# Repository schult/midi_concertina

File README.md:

# MIDI Anglo Concertina

This is a 30-button Anglo Concertina MIDI controller. Click the image below to
watch a short demo:

[Build Instructions](mechanical/README.md)

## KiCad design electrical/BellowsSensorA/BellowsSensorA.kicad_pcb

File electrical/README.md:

# MIDI Concertina - Electrical

These boards are designed to be produced using [JLCPCB](jlcpcb.com)'s Economic
PCBA service. I recommend exporting them with
[Fabrication Toolkit](https://github.com/bennymeg/Fabrication-Toolkit).

## License

[CERN Open Hardware Licence Version 2 - Strongly Reciprocal](LICENSE.txt)

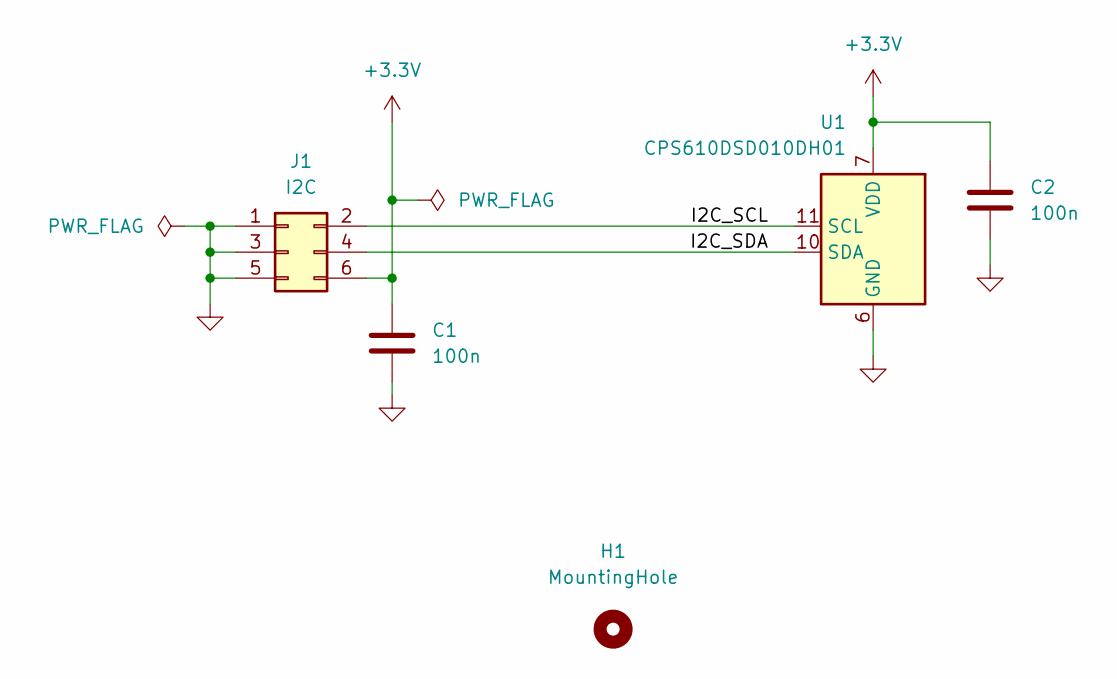
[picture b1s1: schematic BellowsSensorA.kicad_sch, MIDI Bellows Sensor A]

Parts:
C1, C2: 100n; C_0402_1005Metric; Part Samsung CL05B104KO5NNNC; LCSC C1525
H1: MountingHole; MountingHole_3.2mm_M3
J1: I2C; Wuerth_WR-WST_490107670612_2x03_P2.54mm_SKEDD
U1: CPS610DSD010DH01; SOIC-16W_7.5x10.3mm_P1.27mm; Part Consensic CPS610DSD010DH01; LCSC C28646450

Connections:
+3.3V: C1.1, C2.1, J1.6, U1.7 (VDD)
/I2C_SCL: J1.2, U1.11 (SCL)
/I2C_SDA: J1.4, U1.10 (SDA)
GND: C1.2, C2.2, J1.1, J1.3, J1.5, U1.6 (GND)

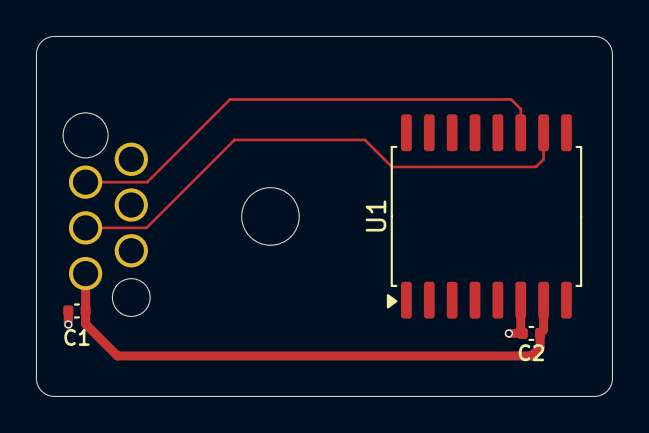
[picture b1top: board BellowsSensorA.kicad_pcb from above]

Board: 2 copper layers, 32.0 x 20.0 mm, 5 parts (1 on the bottom side), 4 nets.

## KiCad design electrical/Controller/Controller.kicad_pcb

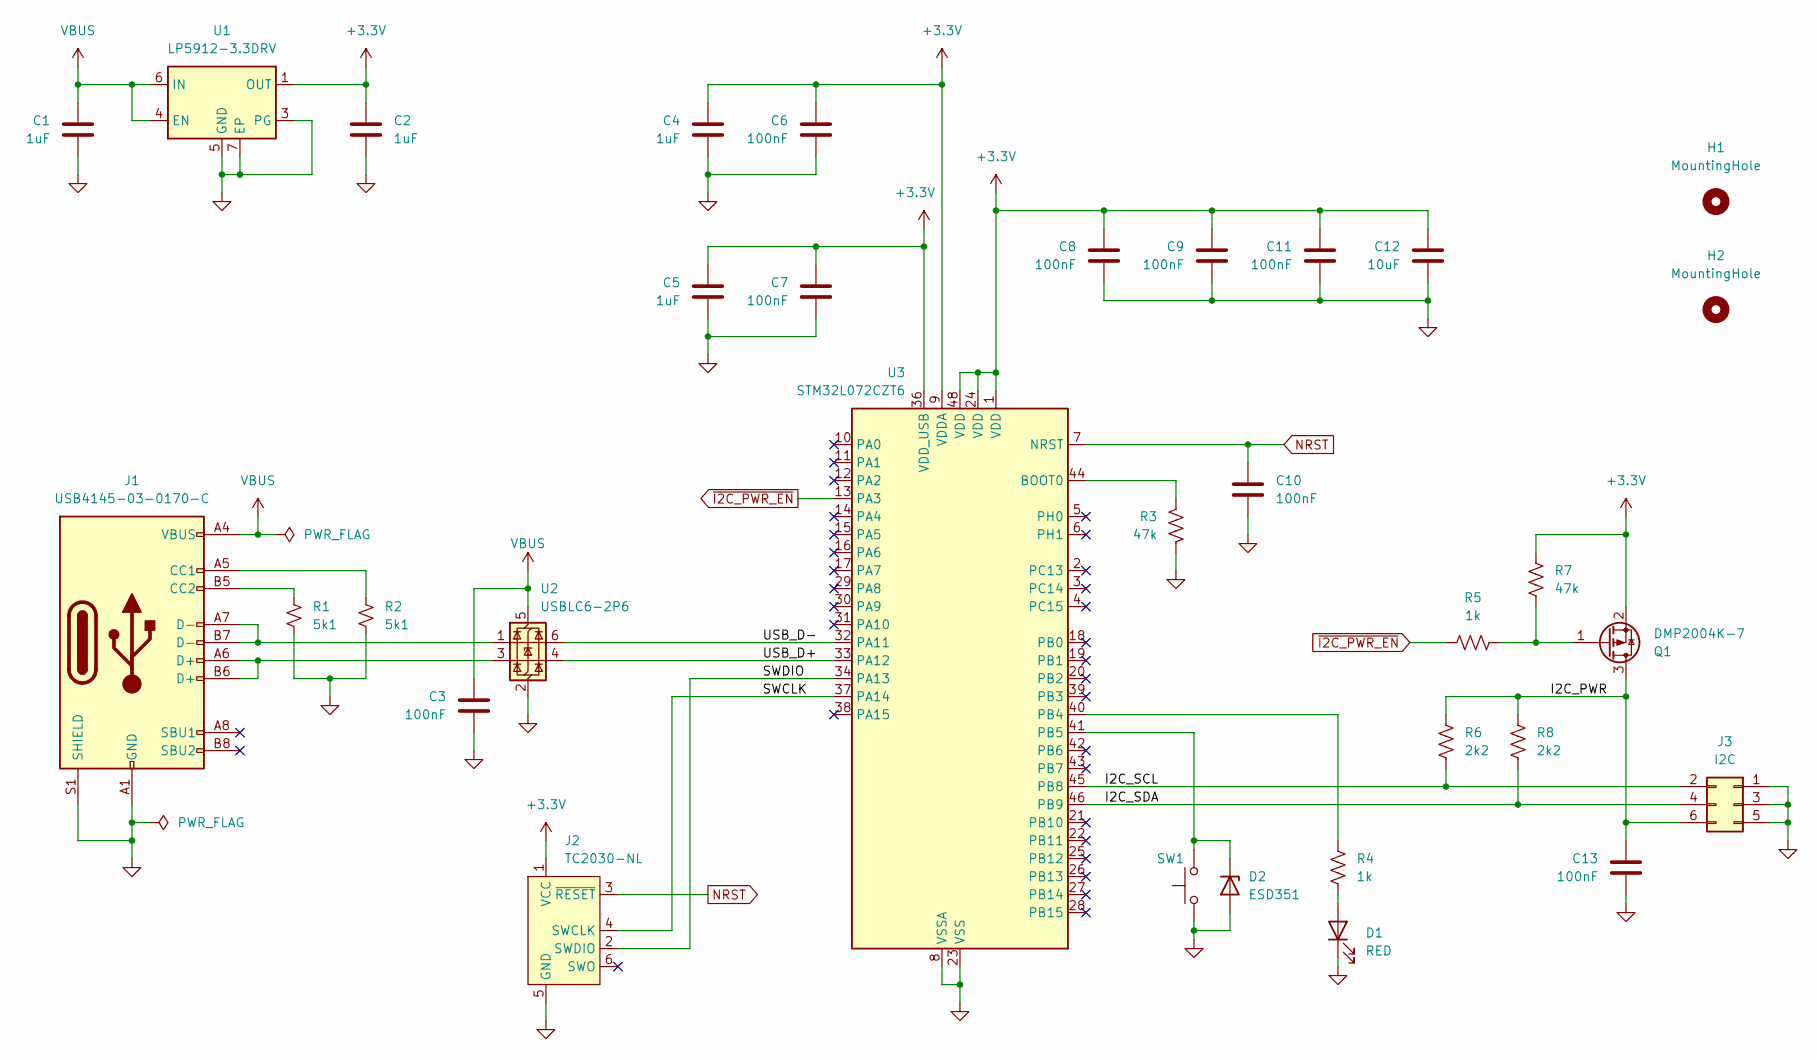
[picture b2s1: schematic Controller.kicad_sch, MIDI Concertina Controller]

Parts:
C1, C2, C4, C5: 1uF; C_0402_1005Metric; Part Samsung CL05A105KA5NQNC; LCSC C52923
C3, C6, C7, C8, C9, C10, C11, C13: 100nF; C_0402_1005Metric; Part Samsung CL05B104KO5NNNC; LCSC C1525
C12: 10uF; C_0603_1608Metric; Part Samsung CL10A106MA8NRNC; LCSC C96446
D1: RED; LED_0603_1608Metric; Part KENTO KT-0603R; LCSC C2286
D2: ESD351; Texas_DPY0002A_0.6x1mm_P0.65mm; Part TI ESD351DPYR; LCSC C1974929
H1, H2: MountingHole; MountingHole_3.2mm_M3
J1: USB4145-03-0170-C; USB_C_Receptacle_GCT-USB4145; Part GCT USB4145-03-0170-C; LCSC C5181332
J2: TC2030-NL; Tag-Connect_TC2030-IDC-NL_2x03_P1.27mm_Vertical
J3: I2C; Wuerth_WR-WST_490107670612_2x03_P2.54mm_SKEDD
Q1: DMP2004K-7; SOT-23; Part Diodes Incorporated DMP2004K-7; LCSC C332297
R1, R2: 5k1; R_0603_1608Metric; Part UNI-ROYAL 0603WAF5101T5E; LCSC C23186
R3, R7: 47k; R_0402_1005Metric; Part UNI-ROYAL 0402WGF4702TCE; LCSC C25792
R4, R5: 1k; R_0402_1005Metric; Part UNI-ROYAL 0402WGF1001TCE; LCSC C11702
R6, R8: 2k2; R_0603_1608Metric; Part UNI-ROYAL 0603WAF2201T5E; LCSC C4190
SW1: SW_Push_1P1T_NO_E-Switch_TL3301NxxxxxG; Part E-Switch TL3301AF160QG; LCSC C273519
U1: LP5912-3.3DRV; WSON-6-1EP_2x2mm_P0.65mm_EP1x1.6mm_ThermalVias; Part TI LP5912-3.3DRVR; LCSC C524780
U2: USBLC6-2P6; SOT-666; Part ST USBLC6-2P6; LCSC C15999
U3: STM32L072CZT6; LQFP-48_7x7mm_P0.5mm; Part STM32L072CZT6; LCSC C1337587

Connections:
+3.3V: C2.1, C4.1, C5.1, C6.1, C7.1, C8.1, C9.1, C11.1, C12.1, J2.1 (VCC), Q1.2 (S), R7.1, U1.1 (OUT), U3.1 (VDD), U3.9 (VDDA), U3.24 (VDD), U3.36 (VDD_USB), U3.48 (VDD)
/I2C_PWR: C13.1, J3.6, Q1.3 (D), R6.1, R8.1
/I2C_SCL: J3.2, R6.2, U3.45 (PB8)
/I2C_SDA: J3.4, R8.2, U3.46 (PB9)
/SWCLK: J2.4 (SWCLK), U3.37 (PA14)
/SWDIO: J2.2 (SWDIO), U3.34 (PA13)
/USB_D+: U2.4 (I/O2), U3.33 (PA12)
/USB_D-: U2.6 (I/O1), U3.32 (PA11)
GND: C1.2, C2.2, C3.2, C4.2, C5.2, C6.2, C7.2, C8.2, C9.2, C10.2, C11.2, C12.2, C13.2, D1.1 (K), D2.2 (A), J1.A1 (GND), J1.A12 (GND), J1.B1 (GND), J1.B12 (GND), J1.S1 (SHIELD), J2.5 (GND), J3.1, J3.3, J3.5, R1.2, R2.2, R3.2, SW1.2, U1.3 (PG), U1.5 (GND), U1.7 (EP), U2.2 (GND), U3.8 (VSSA), U3.23 (VSS), U3.35 (VSS), U3.47 (VSS)
NRST: C10.1, J2.3 (~RESET), U3.7 (NRST)
unnamed: D1.2 (A), R4.2
unnamed: D2.1 (K), SW1.1, U3.41 (PB5)
unnamed: J1.A5 (CC1), R2.1
unnamed: J1.B5 (CC2), R1.1
unnamed: J1.A6 (D+), J1.B6 (D+), U2.3 (I/O2)
unnamed: J1.A7 (D-), J1.B7 (D-), U2.1 (I/O1)
unnamed: Q1.1 (G), R5.2, R7.2
unnamed: R3.1, U3.44 (BOOT0)
unnamed: R4.1, U3.40 (PB4)
VBUS: C1.1, C3.1, J1.A4 (VBUS), J1.A9 (VBUS), J1.B4 (VBUS), J1.B9 (VBUS), U1.4 (EN), U1.6 (IN), U2.5 (VBUS)
~I2C_PWR_EN: R5.1, U3.13 (PA3)

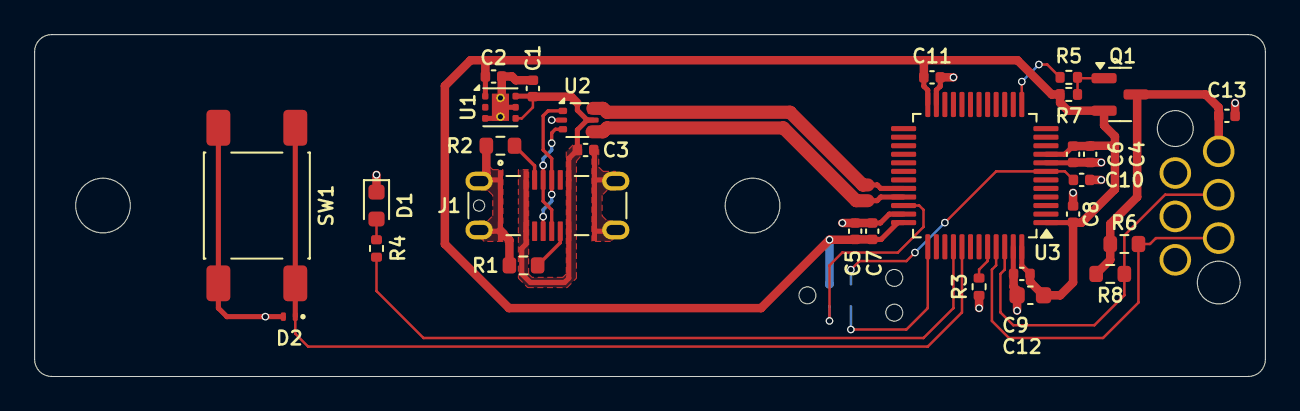
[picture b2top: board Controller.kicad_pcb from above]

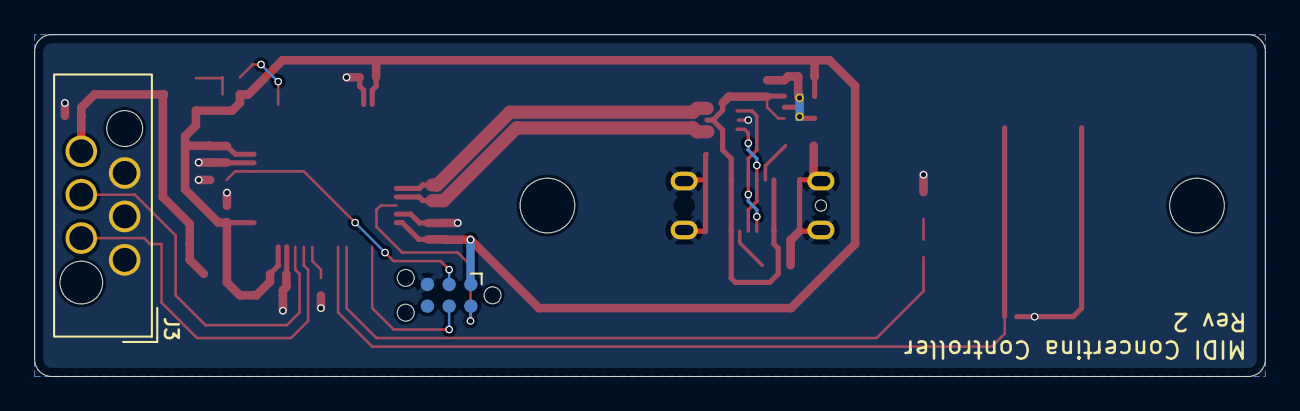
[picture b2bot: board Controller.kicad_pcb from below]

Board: 2 copper layers, 72.0 x 20.0 mm, 33 parts (2 on the bottom side), 21 nets.

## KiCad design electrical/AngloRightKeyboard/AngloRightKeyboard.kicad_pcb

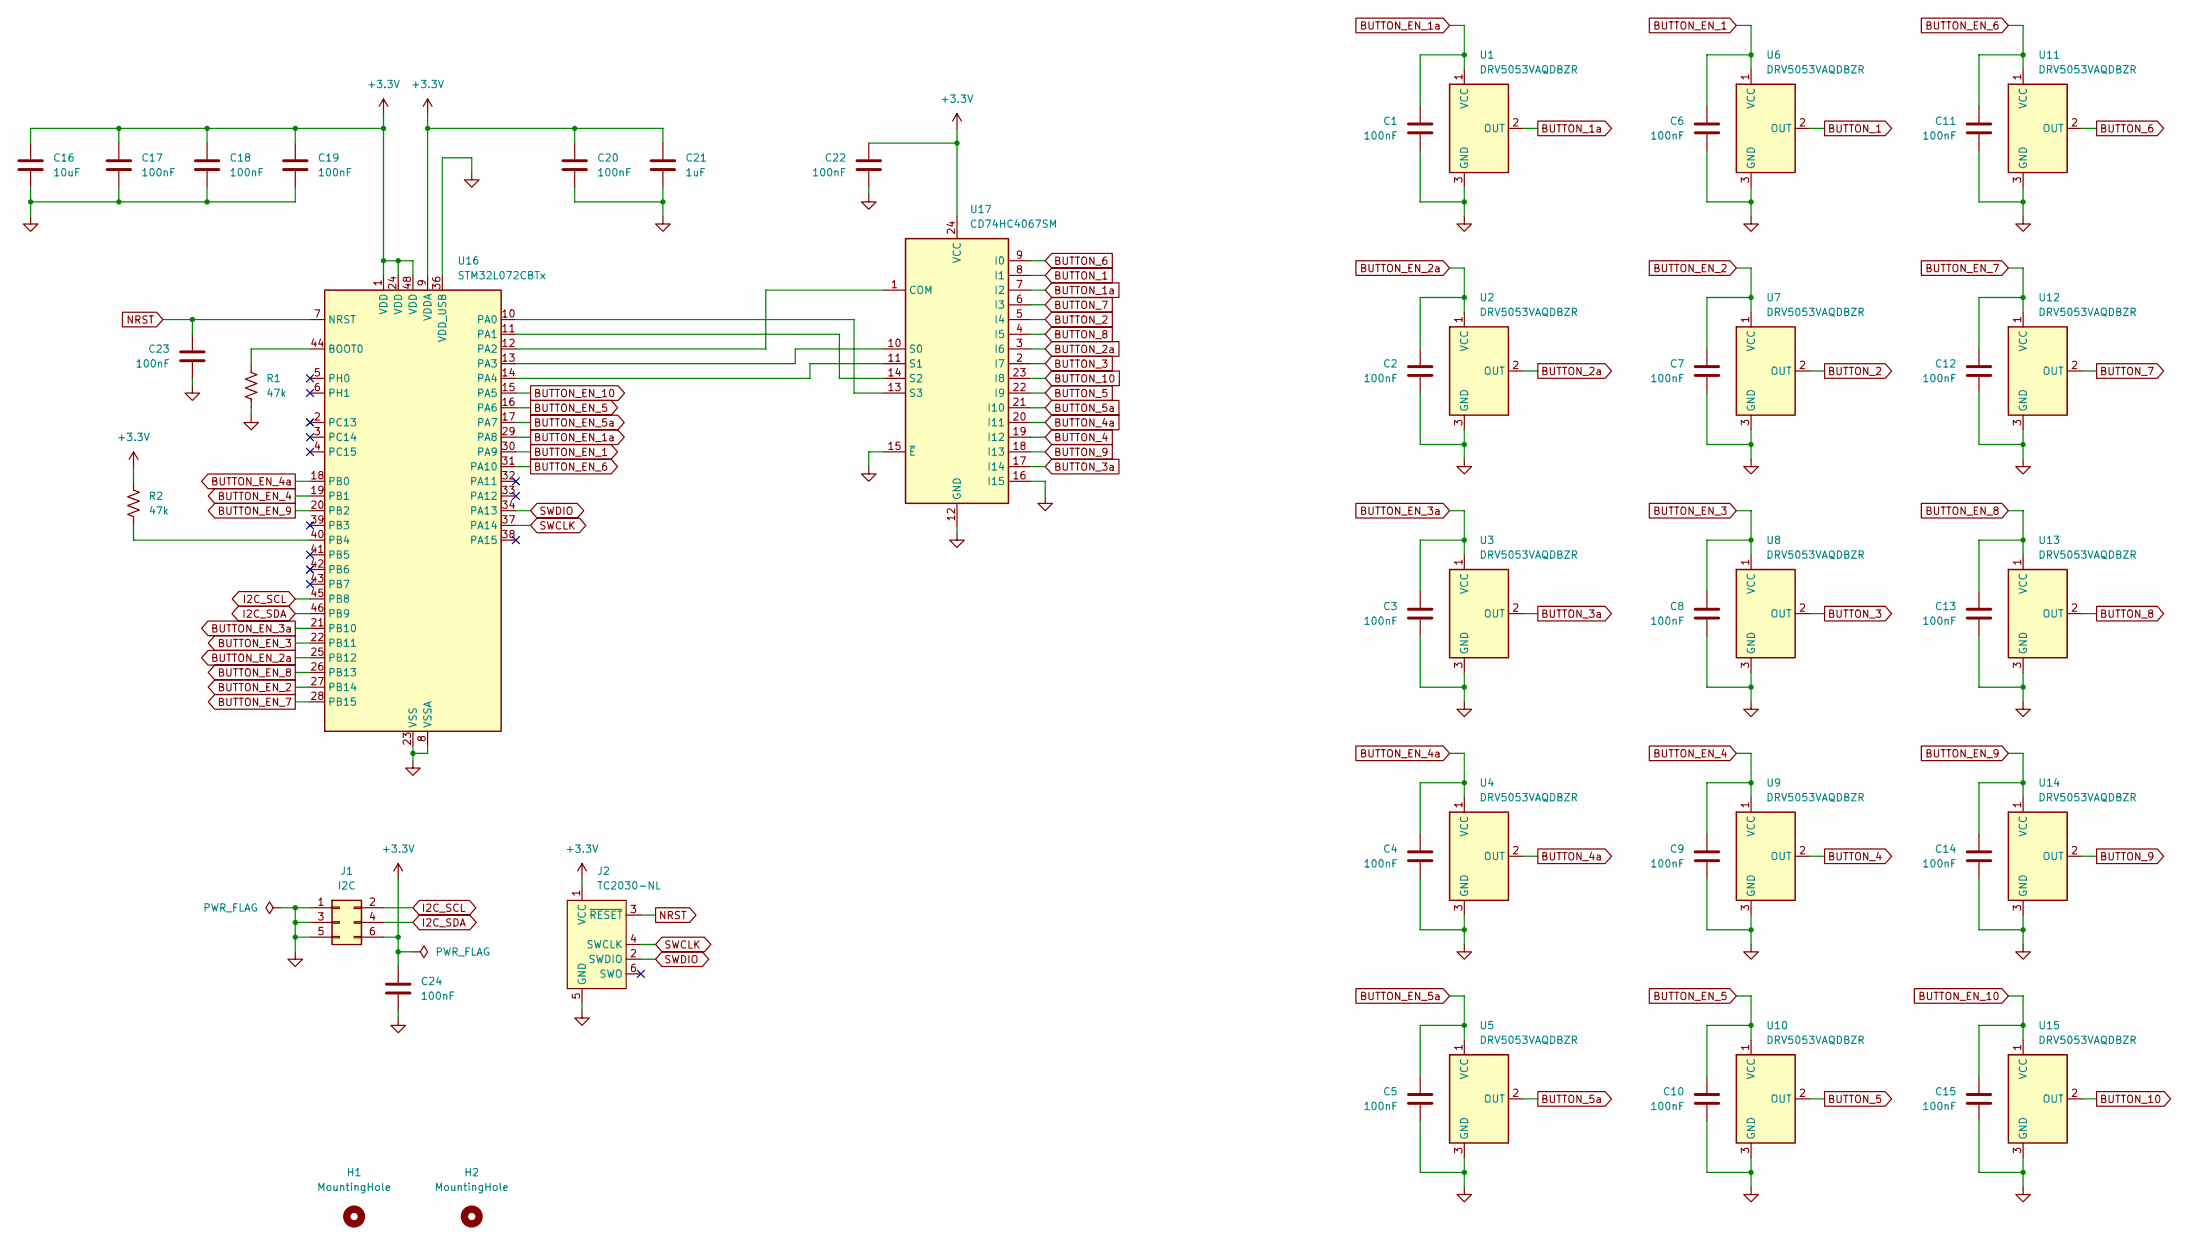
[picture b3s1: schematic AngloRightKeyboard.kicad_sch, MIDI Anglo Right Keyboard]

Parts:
C1, C2, C3, C4, C5, C6, C7, C8, C9, C10, C11, C12, C13, C14, C15, C17, C18, C19, C20, C22, C23, C24: 100nF; C_0402_1005Metric; Part Samsung CL05B104KO5NNNC; LCSC C1525
C16: 10uF; C_0603_1608Metric; Part Samsung CL10A106MA8NRNC; LCSC C96446
C21: 1uF; C_0402_1005Metric; Part Samsung CL05A105KA5NQNC; LCSC C52923
H1, H2: MountingHole; MountingHole_3.2mm_M3
J1: I2C; Wuerth_WR-WST_490107670612_2x03_P2.54mm_SKEDD
J2: TC2030-NL; Tag-Connect_TC2030-IDC-NL_2x03_P1.27mm_Vertical
R1, R2: 47k; R_0402_1005Metric; Part UNI-ROYAL 0402WGF4702TCE; LCSC C25792
U1, U2, U3, U4, U5, U6, U7, U8, U9, U10, U11, U12, U13, U14, U15: DRV5053VAQDBZR; SOT-23; Part TI DRV5053VAQDBZR; LCSC C962159
U16: STM32L072CBTx; LQFP-48_7x7mm_P0.5mm; Part STM32L072CBT6; LCSC C465977
U17: CD74HC4067SM; SSOP-24_5.3x8.2mm_P0.65mm; Part TI CD74HC4067SM96; LCSC C98457

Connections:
+3.3V: C16.1, C17.1, C18.1, C19.1, C20.1, C21.1, C22.1, C24.1, J1.6, J2.1 (VCC), R2.1, U16.1 (VDD), U16.9 (VDDA), U16.24 (VDD), U16.48 (VDD), U17.24 (VCC)
BUTTON_1: U6.2 (OUT), U17.8 (I1)
BUTTON_1a: U1.2 (OUT), U17.7 (I2)
BUTTON_2: U7.2 (OUT), U17.5 (I4)
BUTTON_2a: U2.2 (OUT), U17.3 (I6)
BUTTON_3: U8.2 (OUT), U17.2 (I7)
BUTTON_3a: U3.2 (OUT), U17.17 (I14)
BUTTON_4: U9.2 (OUT), U17.19 (I12)
BUTTON_4a: U4.2 (OUT), U17.20 (I11)
BUTTON_5: U10.2 (OUT), U17.22 (I9)
BUTTON_5a: U5.2 (OUT), U17.21 (I10)
BUTTON_6: U11.2 (OUT), U17.9 (I0)
BUTTON_7: U12.2 (OUT), U17.6 (I3)
BUTTON_8: U13.2 (OUT), U17.4 (I5)
BUTTON_9: U14.2 (OUT), U17.18 (I13)
BUTTON_10: U15.2 (OUT), U17.23 (I8)
BUTTON_EN_1: C6.1, U6.1 (VCC), U16.30 (PA9)
BUTTON_EN_1a: C1.1, U1.1 (VCC), U16.29 (PA8)
BUTTON_EN_2: C7.1, U7.1 (VCC), U16.27 (PB14)
BUTTON_EN_2a: C2.1, U2.1 (VCC), U16.25 (PB12)
BUTTON_EN_3: C8.1, U8.1 (VCC), U16.22 (PB11)
BUTTON_EN_3a: C3.1, U3.1 (VCC), U16.21 (PB10)
BUTTON_EN_4: C9.1, U9.1 (VCC), U16.19 (PB1)
BUTTON_EN_4a: C4.1, U4.1 (VCC), U16.18 (PB0)
BUTTON_EN_5: C10.1, U10.1 (VCC), U16.16 (PA6)
BUTTON_EN_5a: C5.1, U5.1 (VCC), U16.17 (PA7)
BUTTON_EN_6: C11.1, U11.1 (VCC), U16.31 (PA10)
BUTTON_EN_7: C12.1, U12.1 (VCC), U16.28 (PB15)
BUTTON_EN_8: C13.1, U13.1 (VCC), U16.26 (PB13)
BUTTON_EN_9: C14.1, U14.1 (VCC), U16.20 (PB2)
BUTTON_EN_10: C15.1, U15.1 (VCC), U16.15 (PA5)
GND: C1.2, C2.2, C3.2, C4.2, C5.2, C6.2, C7.2, C8.2, C9.2, C10.2, C11.2, C12.2, C13.2, C14.2, C15.2, C16.2, C17.2, C18.2, C19.2, C20.2, C21.2, C22.2, C23.2, C24.2, J1.1, J1.3, J1.5, J2.5 (GND), R1.2, U1.3 (GND), U2.3 (GND), U3.3 (GND), U4.3 (GND), U5.3 (GND), U6.3 (GND), U7.3 (GND), U8.3 (GND), U9.3 (GND), U10.3 (GND), U11.3 (GND), U12.3 (GND), U13.3 (GND), U14.3 (GND), U15.3 (GND), U16.8 (VSSA), U16.23 (VSS), U16.35 (VSS), U16.36 (VDD_USB), U16.47 (VSS), U17.12 (GND), U17.15 (~E), U17.16 (I15)
I2C_SCL: J1.2, U16.45 (PB8)
I2C_SDA: J1.4, U16.46 (PB9)
NRST: C23.1, J2.3 (~RESET), U16.7 (NRST)
unnamed: R1.1, U16.44 (BOOT0)
unnamed: U16.10 (PA0), U17.13 (S3)
unnamed: U16.11 (PA1), U17.14 (S2)
unnamed: U16.12 (PA2), U17.1 (COM)
unnamed: U16.13 (PA3), U17.10 (S0)
unnamed: U16.14 (PA4), U17.11 (S1)
unnamed: R2.2, U16.40 (PB4)
SWCLK: J2.4 (SWCLK), U16.37 (PA14)
SWDIO: J2.2 (SWDIO), U16.34 (PA13)

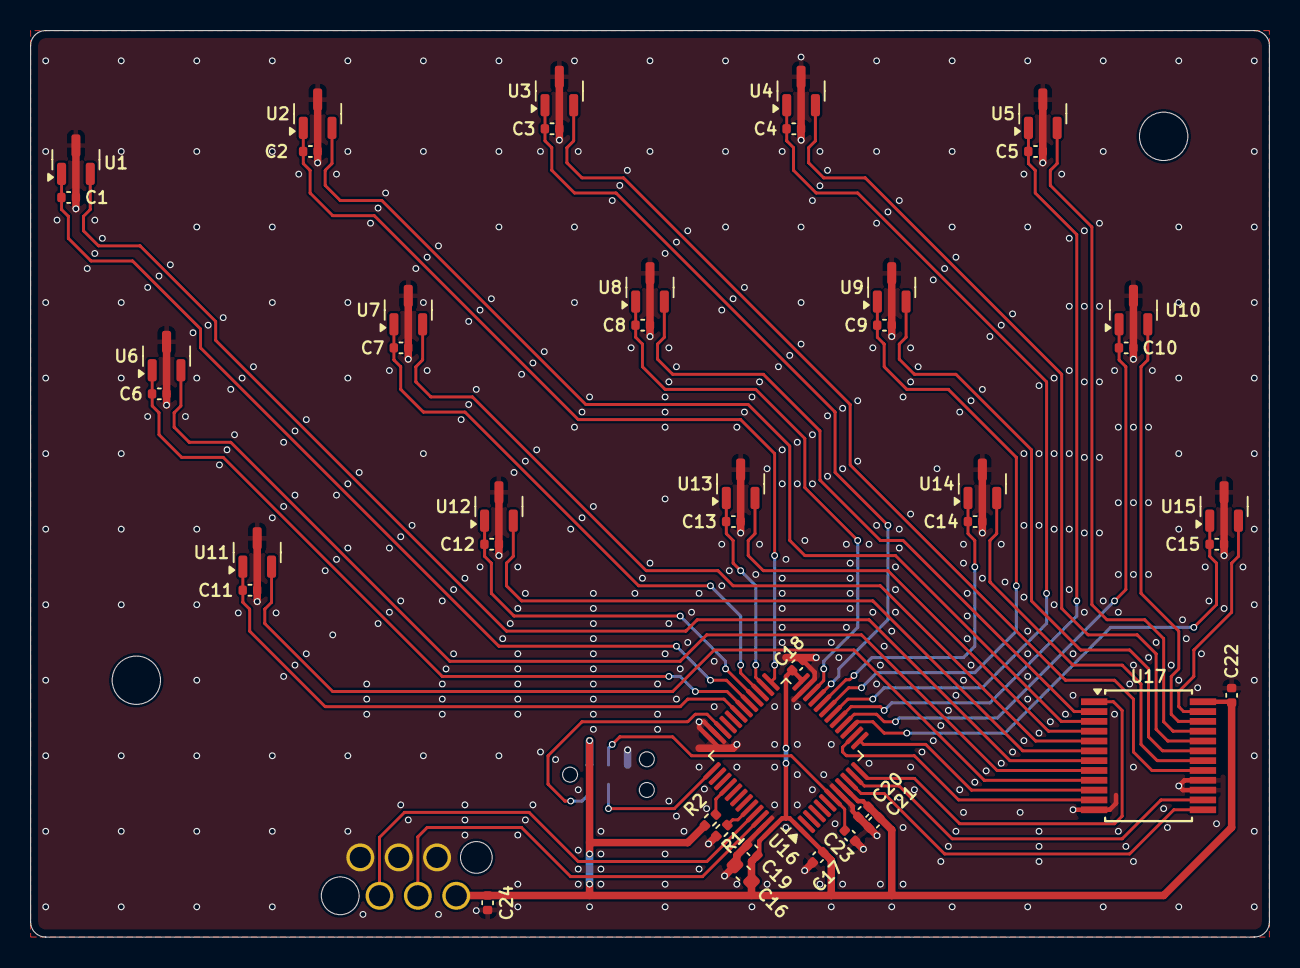
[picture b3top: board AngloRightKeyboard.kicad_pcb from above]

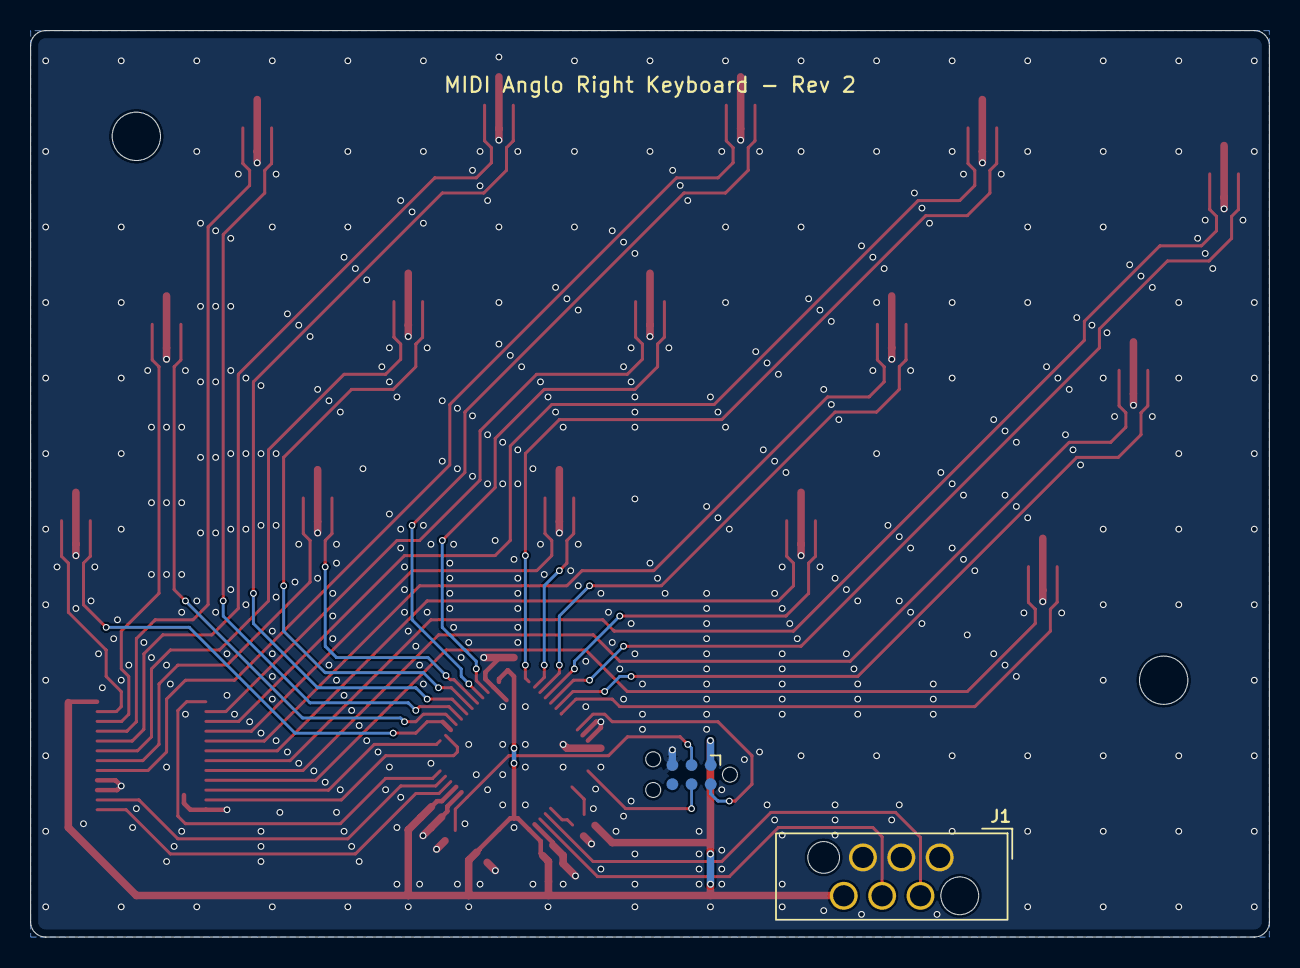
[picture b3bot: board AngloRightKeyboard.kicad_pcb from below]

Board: 2 copper layers, 82.0 x 60.0 mm, 47 parts (2 on the bottom side), 44 nets.

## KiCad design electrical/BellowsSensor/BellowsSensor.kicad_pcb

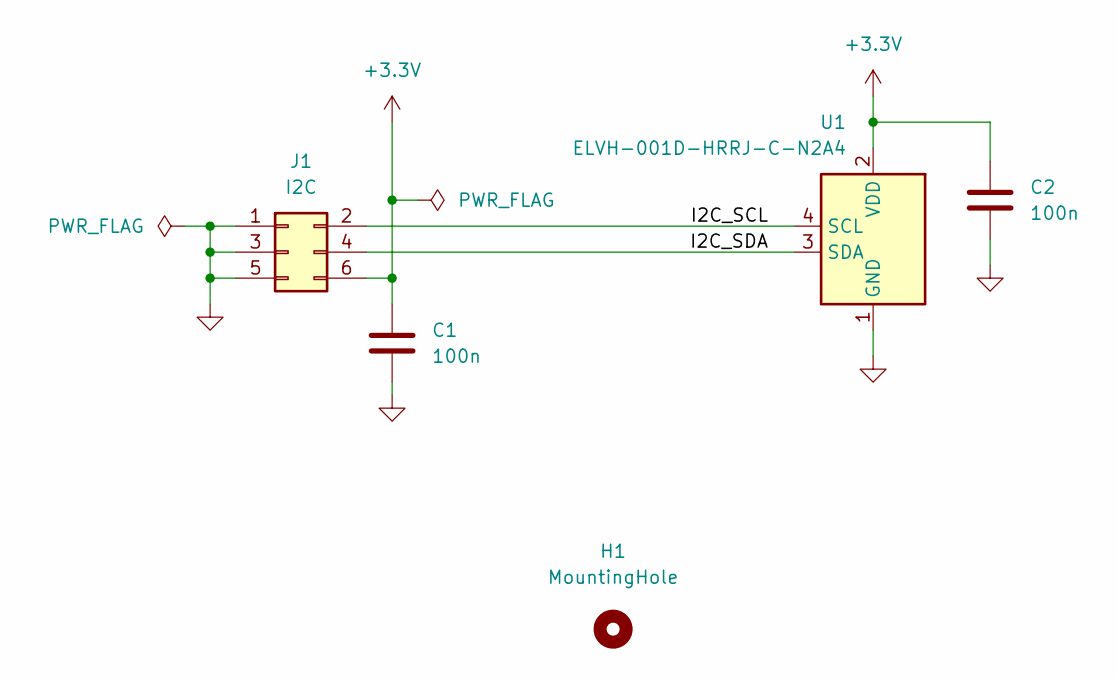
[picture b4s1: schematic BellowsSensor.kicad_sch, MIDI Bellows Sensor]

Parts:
C1, C2: 100n; C_0402_1005Metric; Part Samsung CL05B104KO5NNNC; LCSC C1525
H1: MountingHole; MountingHole_3.2mm_M3
J1: I2C; Wuerth_WR-WST_490107670612_2x03_P2.54mm_SKEDD
U1: ELVH-001D-HRRJ-C-N2A4; Amphenol_ELVH-x-xJ-x-x; Part Amphenol ELVH-001D-HRRJ-C-N2A4; LCSC C3241336

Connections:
+3.3V: C1.1, C2.1, J1.6, U1.2 (VDD)
/I2C_SCL: J1.2, U1.4 (SCL)
/I2C_SDA: J1.4, U1.3 (SDA)
GND: C1.2, C2.2, J1.1, J1.3, J1.5, U1.1 (GND)

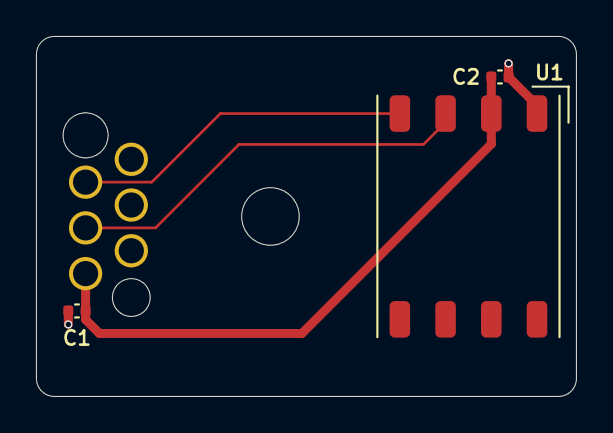
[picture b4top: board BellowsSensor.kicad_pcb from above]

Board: 2 copper layers, 30.0 x 20.0 mm, 5 parts (1 on the bottom side), 4 nets.

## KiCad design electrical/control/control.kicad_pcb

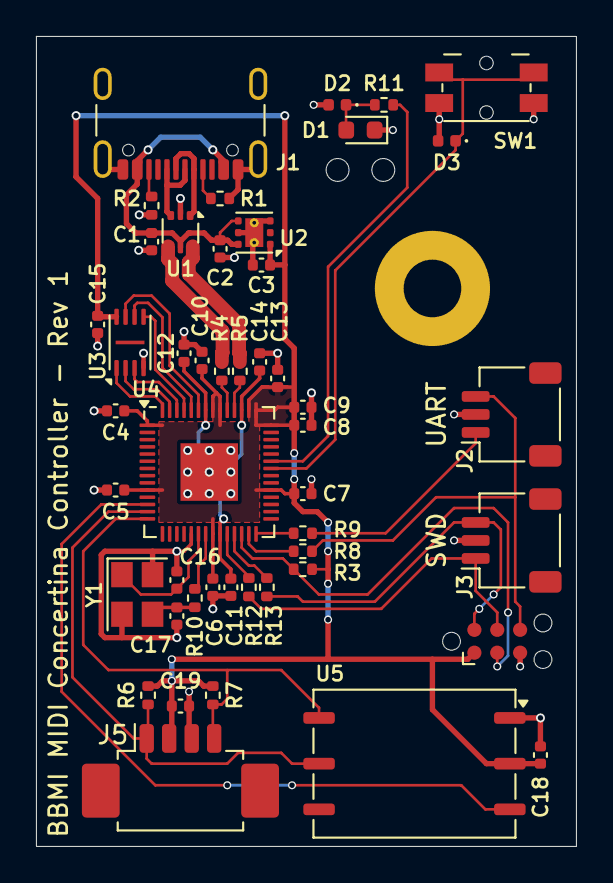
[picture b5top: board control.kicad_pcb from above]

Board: 2 copper layers, 30.0 x 45.0 mm, 49 parts (0 on the bottom side), 36 nets.

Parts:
C1, C4, C5, C6, C7, C8, C9, C10, C11, C12, C15, C18, C19: 100n; C_0402_1005Metric
C2, C3, C13, C14: 1uF; C_0402_1005Metric
C16, C17: 15p; C_0402_1005Metric
D1: RED; LED_0603_1608Metric
D2, D3: ESD351; D_0402_1005Metric
H1: MountingHole; MountingHole_3.2mm_M3_Pad
H2: SLP-150-150-F; SLP3-150-150-F
J1: USB4105-GF-A; USB_C_Receptacle_GCT_USB4105-xx-A_16P_TopMnt_Horizontal
J2: UART; JST_SH_SM03B-SRSS-TB_1x03-1MP_P1.00mm_Horizontal
J3: SWD; JST_SH_SM03B-SRSS-TB_1x03-1MP_P1.00mm_Horizontal
J4: TC2030-NL; Tag-Connect_TC2030-IDC-NL_2x03_P1.27mm_Vertical
J5: I2C; Molex_PicoBlade_53261-0471_1x04-1MP_P1.25mm_Horizontal
R1, R2: 5k1; R_0402_1005Metric
R3, R10, R11: 1k; R_0402_1005Metric
R4, R5: 27R; R_0402_1005Metric
R6, R7: 2k2; R_0402_1005Metric
R8, R9, R12, R13: 100R; R_0402_1005Metric
SW1: SYS; Panasonic_EVQPUL_EVQPUC
U1: USBLC6-2P6; SOT-666
U2: LP5912-3.3DRV; WSON-6-1EP_2x2mm_P0.65mm_EP1x1.6mm_ThermalVias
U3: W25Q16JVUXIQ; Winbond_USON-8-1EP_3x2mm_P0.5mm_EP0.2x1.6mm
U4: RP2040; QFN-56-1EP_7x7mm_P0.4mm_EP3.2x3.2mm
U5: ABPMRRV060MG2A3; Honeywell_ABPMRRx
Y1: ABM8-272-T3; Crystal_SMD_3225-4Pin_3.2x2.5mm

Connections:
+1V1: C11.1, C12.1, C14.1, U4.23 (DVDD), U4.45 (VREG_VOUT), U4.50 (DVDD)
+3.3V: C3.1, C4.1, C5.1, C6.1, C7.1, C8.1, C9.1, C10.1, C13.1, C15.1, C18.1, C19.1, J4.1 (VCC), J5.2, R3.1, R6.1, R7.1, U2.1 (OUT), U3.8 (VCC), U4.1 (IOVDD), U4.10 (IOVDD), U4.22 (IOVDD), U4.33 (IOVDD), U4.42 (IOVDD), U4.43 (ADC_AVDD), U4.44 (VREG_IN), U4.48 (USB_VDD), U4.49 (IOVDD), U5.2 (VDD)
/QSPI_SCLK: U3.6 (CLK), U4.52 (QSPI_SCLK)
/QSPI_SD0: U3.5 (DI/IO_{0}), U4.53 (QSPI_SD0)
/QSPI_SD1: U3.2 (DO/IO_{1}), U4.55 (QSPI_SD1)
/QSPI_SD2: U3.3 (~WP/IO_{2}), U4.54 (QSPI_SD2)
/QSPI_SD3: U3.7 (~HOLD/~RESET/IO_{3}), U4.51 (QSPI_SD3)
/QSPI_SS: U3.1 (~CS), U4.56 (QSPI_SS)
GND: C1.2, C2.2, C3.2, C4.2, C5.2, C6.2, C7.2, C8.2, C9.2, C10.2, C11.2, C12.2, C13.2, C14.2, C15.2, C16.2, C17.2, C18.2, C19.2, D1.1 (K), D2.2 (A), D3.2 (A), H1.1, J1.A1 (GND), J1.A12 (GND), J1.B1 (GND), J1.B12 (GND), J1.S1 (SHIELD), J2.2, J3.2, J4.5 (GND), J5.3, R1.2, R2.2, SW1.2, U1.2 (GND), U2.3 (PG), U2.5 (GND), U2.7 (EP), U3.4 (GND), U4.19 (TESTEN), U4.57 (GND), U5.1 (GND), Y1.2, Y1.4
I2C_SCL: J5.4, R7.2, U4.14 (GPIO11), U5.6 (SCL)
I2C_SDA: J5.1, R6.2, U4.13 (GPIO10), U5.5 (SDA)
unnamed: C17.1, R10.1, Y1.3
unnamed: D1.2 (A), D2.1 (K), R11.2
unnamed: D3.1 (K), SW1.1, U4.36 (GPIO24)
unnamed: J1.A5 (CC1), R1.1
unnamed: J1.B5 (CC2), R2.1
unnamed: J1.A6 (D+), J1.B6 (D+), U1.3 (I/O2)
unnamed: J1.A7 (D-), J1.B7 (D-), U1.1 (I/O1)
unnamed: R8.1, U4.27 (GPIO16)
unnamed: R9.1, U4.28 (GPIO17)
unnamed: R11.1, U4.37 (GPIO25)
unnamed: R12.1, U4.24 (SWCLK)
unnamed: R13.1, U4.25 (SWD)
unnamed: R5.1, U4.46 (USB_DM)
unnamed: R4.1, U4.47 (USB_DP)
unnamed: C16.1, U4.20 (XIN), Y1.1
unnamed: R10.2, U4.21 (XOUT)
PRESSURE_INT: U4.12 (GPIO9), U5.3 (INT)
RUN: J4.3 (~RESET), R3.2, U4.26 (RUN)
SWCLK: J3.1, J4.4 (SWCLK), R12.2
SWDIO: J3.3, J4.2 (SWDIO), R13.2
UART_RX: J2.1, R9.2
UART_TX: J2.3, J4.6 (SWO), R8.2
USB_D+: R4.2, U1.4 (I/O2)
USB_D-: R5.2, U1.6 (I/O1)
VBUS: C1.1, C2.1, J1.A4 (VBUS), J1.A9 (VBUS), J1.B4 (VBUS), J1.B9 (VBUS), U1.5 (VBUS), U2.4 (EN), U2.6 (IN)

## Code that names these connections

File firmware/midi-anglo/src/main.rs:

#![no_std]
#![no_main]

use defmt_rtt as _;
use embassy_stm32::adc::AdcChannel;
use embassy_stm32::{adc, bind_interrupts, gpio, i2c, peripherals, rcc, time::khz, Peri};
use embassy_sync::blocking_mutex::raw::ThreadModeRawMutex;
use embassy_sync::signal::Signal;
use embassy_time::{Duration, Ticker};
use panic_probe as _;

bind_interrupts!(struct Irqs {
    ADC1_COMP => adc::InterruptHandler<peripherals::ADC1>;
    I2C1 => i2c::EventInterruptHandler<peripherals::I2C1>, i2c::ErrorInterruptHandler<peripherals::I2C1>;
});

const BUTTON_COUNT: usize = 15;
const MUX_PINS: usize = 4;

enum Chirality {
    Left,
    Right,
}

struct Mux<'a, const N: usize> {
    out: [gpio::Output<'a>; N],
}

impl<'a, const N: usize> Mux<'a, N> {
    pub fn new(pins: [Peri<'static, gpio::AnyPin>; N]) -> Self {
        Self {
            out: pins.map(|p| gpio::Output::new(p, gpio::Level::Low, gpio::Speed::Medium)),
        }
    }

    pub fn select(&mut self, index: usize) {
        for bit in 0..self.out.len() {
            self.out[bit].set_level(match (index >> bit) & 1 {
                0 => gpio::Level::Low,
                _ => gpio::Level::High,
            });
        }
    }
}

struct ButtonConfig<'a> {
    power: gpio::Output<'a>,
    index: usize,
}

impl<'a> ButtonConfig<'a> {
    pub fn new(power_pin: Peri<'a, impl gpio::Pin>, index: usize) -> Self {
        Self {
            power: gpio::Output::new(power_pin, gpio::Level::Low, gpio::Speed::Low),
            index,
        }
    }

    pub fn enable(&mut self) {
        self.power.set_high();
    }

    pub fn disable(&mut self) {
        self.power.set_low();
    }

    pub fn index(&mut self) -> usize {
        self.index
    }
}

static BUTTON_STATE_SIGNAL: Signal<ThreadModeRawMutex, u16> = Signal::new();

#[embassy_executor::main]
async fn main(spawner: embassy_executor::Spawner) {
    let mut config = embassy_stm32::Config::default();
    config.rcc.hsi = true;
    config.rcc.sys = rcc::Sysclk::HSI;
    let p = embassy_stm32::init(config);

    let chirality_in = gpio::Input::new(p.PB4, gpio::Pull::None);
    let chirality = if chirality_in.is_low() {
        Chirality::Left
    } else {
        Chirality::Right
    };


    // Right hand mapping
    let buttons = match chirality {
        Chirality::Left => [
            ButtonConfig::new(p.PB12, 6),  // 1a
            ButtonConfig::new(p.PB10, 14), // 2a
            ButtonConfig::new(p.PB0, 11),  // 3a
            ButtonConfig::new(p.PA6, 9),   // 4a
            ButtonConfig::new(p.PA5, 8),   // 5a
            ButtonConfig::new(p.PA9, 1),   // 1
            ButtonConfig::new(p.PB15, 3),  // 2
            ButtonConfig::new(p.PB11, 7),  // 3
            ButtonConfig::new(p.PB1, 12),  // 4
            ButtonConfig::new(p.PA7, 10),  // 5
            ButtonConfig::new(p.PA10, 0),  // 6
            ButtonConfig::new(p.PA8, 2),   // 7
            ButtonConfig::new(p.PB14, 4),  // 8
            ButtonConfig::new(p.PB13, 5),  // 9
            ButtonConfig::new(p.PB2, 13),  // 10
        ],
        Chirality::Right => [
            ButtonConfig::new(p.PA8, 2),   // 1a
            ButtonConfig::new(p.PB12, 6),  // 2a
            ButtonConfig::new(p.PB10, 14), // 3a
            ButtonConfig::new(p.PB0, 11),  // 4a
            ButtonConfig::new(p.PA7, 10),  // 5a
            ButtonConfig::new(p.PA9, 1),   // 1
            ButtonConfig::new(p.PB14, 4),  // 2
            ButtonConfig::new(p.PB11, 7),  // 3
            ButtonConfig::new(p.PB1, 12),  // 4
            ButtonConfig::new(p.PA6, 9),   // 5
            ButtonConfig::new(p.PA10, 0),  // 6
            ButtonConfig::new(p.PB15, 3),  // 7
            ButtonConfig::new(p.PB13, 5),  // 8
            ButtonConfig::new(p.PB2, 13),  // 9
            ButtonConfig::new(p.PA5, 8),   // 10
        ],
    };

    let mux = Mux::new([p.PA3.into(), p.PA4.into(), p.PA1.into(), p.PA0.into()]);

    let mut adc1 = adc::Adc::new(p.ADC1, Irqs);
    adc1.set_sample_time(adc::SampleTime::CYCLES160_5);
    let adc_pin = p.PA2;

    spawner.spawn(button_scan_task(buttons, mux, adc1, adc_pin.degrade_adc())).unwrap();


    let mut i2c_config = i2c::Config::default();
    i2c_config.sda_pullup = false;
    i2c_config.scl_pullup = false;
    // TODO: Increase frequency after fixing controller hardware.
    i2c_config.frequency = khz(10);

    let i2c_master = i2c::I2c::new(
        p.I2C1,
        p.PB8, // SCL
        p.PB9, // SDA
        Irqs,
        p.DMA1_CH2, // TX DMA
        p.DMA1_CH3, // RX DMA
        i2c_config,
    );

    let i2c_addr = match chirality {
        Chirality::Left => 0x22,
        Chirality::Right => 0x23,
    };
    let slave_config = i2c::SlaveAddrConfig::basic(i2c_addr);
    let mut i2c_slave = i2c_master.into_slave_multimaster(slave_config);

    let mut response_buffer = [0u8; 2];
    loop {
        match i2c_slave.listen().await {
            Ok(i2c::SlaveCommand {
                kind: i2c::SlaveCommandKind::Read,
                address: _,
            }) => {
                let update = BUTTON_STATE_SIGNAL.try_take();
                if let Some(state) = update {
                    response_buffer = state.to_be_bytes();
                }
                let _ = i2c_slave.respond_to_read(&response_buffer).await;
            },
            _ => (),
        }
    }
}

#[embassy_executor::task]
async fn button_scan_task(
    mut buttons: [ButtonConfig<'static>; BUTTON_COUNT],
    mut mux: Mux<'static, MUX_PINS>,
    mut adc: adc::Adc<'static, peripherals::ADC1>,
    mut adc_pin: adc::AnyAdcChannel<peripherals::ADC1>
) {
    // Allow for DRV5053 power-up. Duration is max turn-on time divided by number of simultaneously
    // powered sensors.
    let mut ticker = Ticker::every(Duration::from_micros(25));

    let mut i = 0;
    buttons[i].enable();
    ticker.next().await;

    let mut state = 0u16;

    loop {
        let next_i = (i + 1) % buttons.len();
        buttons[next_i].enable();
        ticker.next().await;

        mux.select(buttons[i].index());

        let raw = adc.read(&mut adc_pin).await;
        if raw < 600 {
            state |= 1<<i;
        } else {
            state &= !(1<<i);
        }
        BUTTON_STATE_SIGNAL.signal(state);

        buttons[i].disable();
        i = next_i;
    }
}

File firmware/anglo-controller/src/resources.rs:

use assign_resources::assign_resources;
use embassy_stm32::{Peri, bind_interrupts, dma, exti, i2c, interrupt, peripherals, usb};

bind_interrupts!(pub struct Irqs {
    USB => usb::InterruptHandler<peripherals::USB>;
    I2C1 => i2c::EventInterruptHandler<peripherals::I2C1>, i2c::ErrorInterruptHandler<peripherals::I2C1>;
    DMA1_CHANNEL2_3 => dma::InterruptHandler<peripherals::DMA1_CH2>, dma::InterruptHandler<peripherals::DMA1_CH3>;
    EXTI4_15 => exti::InterruptHandler<interrupt::typelevel::EXTI4_15>;
});

assign_resources! {
    dfu: DfuResources {
        flash: FLASH,
    }
    led: LedResources {
        pin: PB4,
        timer: TIM3,
    }
    button: ButtonResources {
        pin: PB5,
        channel: EXTI5,
    }
    i2c: I2cResources {
        i2c: I2C1,
        scl: PB8,
        sda: PB9,
        tx_dma: DMA1_CH2,
        rx_dma: DMA1_CH3,
        power: PA3,
    }
    usb: UsbResources {
        usb: USB,
        dp: PA12,
        dm: PA11,
    }
}

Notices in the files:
electrical/AngloRightKeyboard/AngloRightKeyboard.kicad_pcb:
Licensed under CERN-OHL-S v2 or any later version
Copyright 2025 Steven Schulteis
